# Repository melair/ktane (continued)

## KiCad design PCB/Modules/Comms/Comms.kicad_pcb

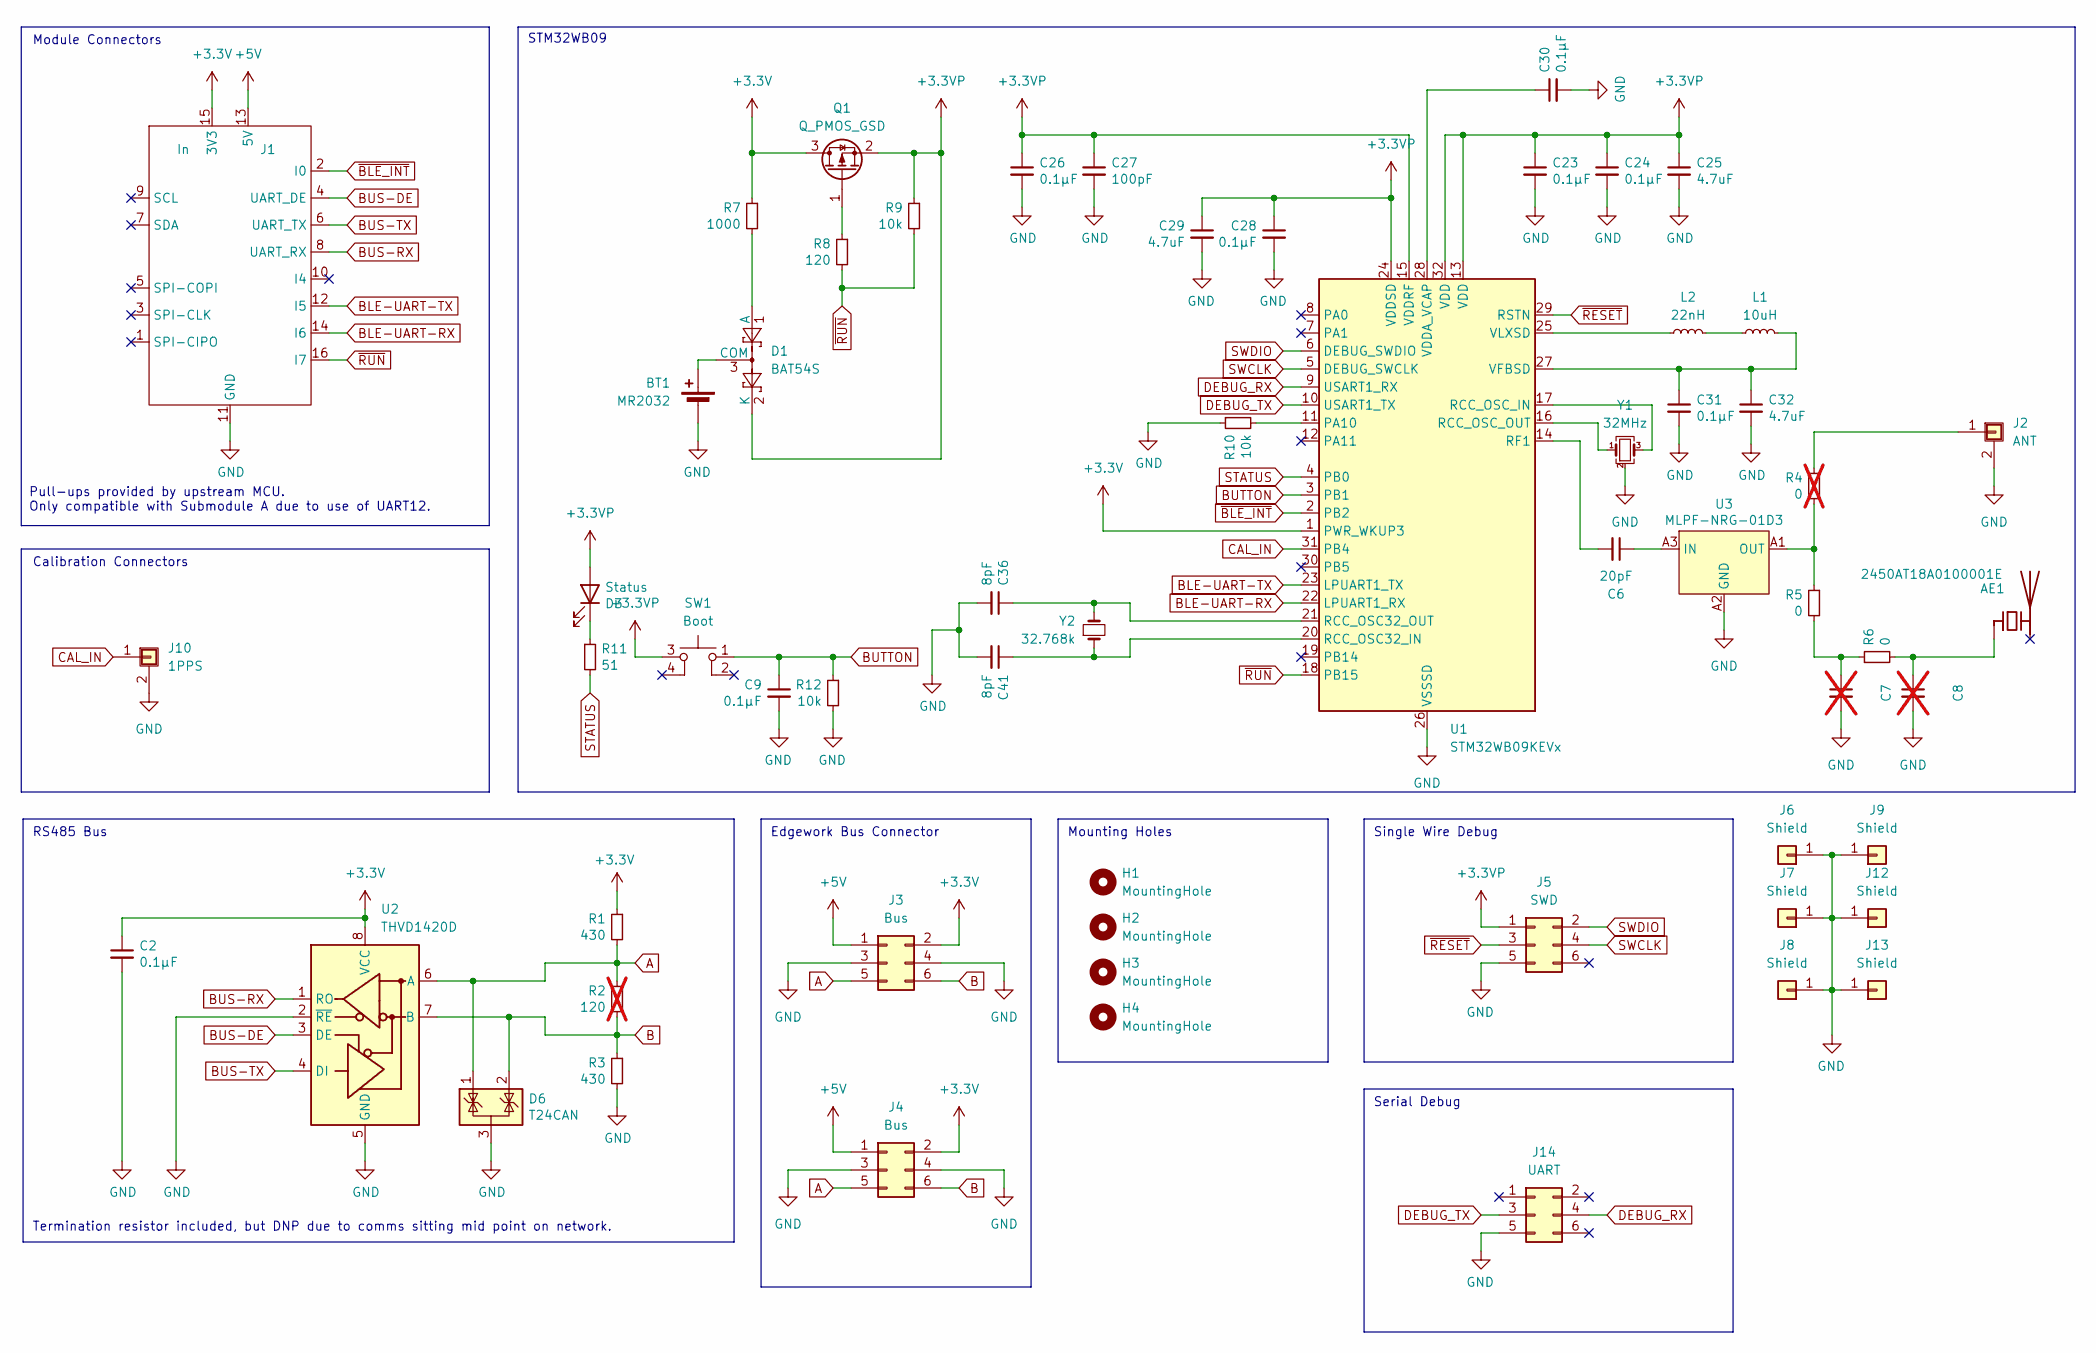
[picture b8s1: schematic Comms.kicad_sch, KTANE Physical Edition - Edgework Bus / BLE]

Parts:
AE1: 2450AT18A0100001E; Johanson_2450AT18x100_2400-2500Mhz; DIGIKEY 712-2450AT18A0100001ECT-ND
BT1: MR2032; CellHolder
C2, C9, C23, C24, C26, C28, C30, C31: 0.1μF; C_0603_1608Metric; DIGIKEY 1276-1005-1-ND
C6: 20pF; R_0402_1005Metric_Tweaked; DIGIKEY 1276-6601-1-ND
C7, C8: R_0402_1005Metric_Tweaked; DIGIKEY NONE; not fitted
C25, C29, C32: 4.7uF; C_0603_1608Metric; DIGIKEY 1276-2087-1-ND
C27: 100pF; C_0603_1608Metric; DIGIKEY 1276-1005-1-ND
C36, C41: 8pF; C_0603_1608Metric; DIGIKEY 490-GCM1885C2A8R0BA16JCT-ND
D1: BAT54S; SOT-23; DIGIKEY BAT54SLT1GOSCT-ND
D3: Status; LED_0603_1608Metric; DIGIKEY 160-1827-1-ND
D6: T24CAN; SOT-23; DIGIKEY STOCK
H1, H2, H3, H4: MountingHole; MountingHole_3.2mm_M3_NoCopper; DIGIKEY NONE
J1: In; PinHeader_2x08_P2.54mm_Vertical-Centered; DIGIKEY S9171-ND
J2: ANT; U.FL_Hirose_U.FL-R-SMT-1_Vertical; DIGIKEY 26-U.FL-R-SMT-1(32)CT-ND
J3, J4: Bus; PinHeader_2x03_P2.54mm_Vertical-Centered; DIGIKEY S9716-ND
J5: SWD; Tag-Connect_TC2030-IDC-NL_2x03_P1.27mm_Vertical; DIGIKEY NONE
J6, J7, J8, J9: Shield; EMI_Shield_Corner; DIGIKEY STOCK/AliExpress
J10: 1PPS; U.FL_Hirose_U.FL-R-SMT-1_Vertical; DIGIKEY 26-U.FL-R-SMT-1(32)CT-ND
J12, J13: Shield; EMI_Shield_Straight; DIGIKEY STOCK/AliExpress
J14: UART; Tag-Connect_TC2030-IDC-NL_2x03_P1.27mm_Vertical; DIGIKEY NONE
L1: 10uH; L_0805_2012Metric; DIGIKEY 490-LQM21DN100M70LCT-ND
L2: 22nH; L_0402_1005Metric; DIGIKEY 490-LQG15HN22NG02DCT-ND
Q1: Q_PMOS_GSD; SOT-23; DIGIKEY 4518-SI2307ACT-ND
R1, R3: 430; R_0603_1608Metric; DIGIKEY P430HCT-ND
R2: 120; R_0603_1608Metric; DIGIKEY P120HCT-ND; not fitted
R4: 0; R_0402_1005Metric_Tweaked; DIGIKEY 10-ERJ-H2G0R00XCT-ND; not fitted
R5, R6: 0; R_0402_1005Metric_Tweaked; DIGIKEY 10-ERJ-H2G0R00XCT-ND
R7: 1000; R_0603_1608Metric; DIGIKEY P1.00KHCT-ND
R8: 120; R_0603_1608Metric; DIGIKEY P120HCT-ND
R9, R10, R12: 10k; R_0603_1608Metric; DIGIKEY P10.0KHCT-ND
R11: 51; R_0603_1608Metric; DIGIKEY P51.0HCT-ND
SW1: Boot; PTS526Sx15SMTR2xLFS; DIGIKEY CKN12220-1-ND
U1: STM32WB09KEVx; QFN-32-1EP_5x5mm_P0.5mm_EP3.7x3.7mm; DIGIKEY 497-STM32WB09KEV6TRCT-ND
U2: THVD1420D; SOT-583-8; DIGIKEY 296-THVD1420DRLRCT-ND
U3: MLPF-NRG-01D3; DIGIKEY 497-MLPF-NRG-01D3CT-ND
Y1: 32MHz; Crystal_SMD_2016-4Pin_2.0x1.6mm; DIGIKEY 644-CS06654-32MCT-ND
Y2: 32.768k; Crystal_SMD_2012-2Pin_2.0x1.2mm; DIGIKEY XC3096CT-ND

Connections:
+3.3V: C2.1, J1.15 (3V3), J3.2, J4.2, Q1.3 (D), R1.1, R7.1, U1.1 (PWR_WKUP3), U2.8 (VCC)
+3.3VP: C23.1, C24.1, C25.1, C26.1, C27.1, C28.1, C29.1, D1.2 (K), D3.2 (A), J5.1, Q1.2 (S), R9.1, SW1.3, U1.13 (VDD), U1.15 (VDDRF), U1.24 (VDDSD), U1.32 (VDD)
+5V: J1.13 (5V), J3.1, J4.1
A: D6.1 (K), J3.5, J4.5, R1.2, R2.1, U2.6 (A)
B: D6.2 (K), J3.6, J4.6, R2.2, R3.1, U2.7 (B)
BLE-UART-RX: J1.14 (I6), U1.22 (LPUART1_RX)
BLE-UART-TX: J1.12 (I5), U1.23 (LPUART1_TX)
BUS-DE: J1.4 (UART_DE), U2.3 (DE)
BUS-RX: J1.8 (UART_RX), U2.1 (RO)
BUS-TX: J1.6 (UART_TX), U2.4 (DI)
BUTTON: C9.1, R12.1, SW1.1, U1.3 (PB1)
CAL_IN: J10.1, U1.31 (PB4)
DEBUG_RX: J14.4, U1.9 (USART1_RX)
DEBUG_TX: J14.3, U1.10 (USART1_TX)
GND: BT1.2 (-), C2.2, C7.2, C8.2, C9.2, C23.2, C24.2, C25.2, C26.2, C27.2, C28.2, C29.2, C30.2, C31.2, C32.2, C36.2, C41.2, D6.3 (A), J1.11 (GND), J2.2 (Shield), J3.3, J3.4, J4.3, J4.4, J5.5, J6.1 (Pin_1_1), J7.1 (Pin_1_1), J8.1 (Pin_1_1), J9.1 (Pin_1_1), J10.2 (Shield), J12.1 (Pin_1_1), J13.1 (Pin_1_1), J14.5, R3.2, R10.1, R12.2, U1.26 (VSSSD), U1.33 (VSSSD), U2.2 (~RE), U2.5 (GND), U3.A2 (GND), U3.B1 (GND), U3.B2 (GND), U3.B3 (GND), Y1.2 (G), Y1.4 (G)
unnamed: AE1.1 (FEED_1), C8.1, R6.2
unnamed: BT1.1 (+), D1.3 (COM)
unnamed: C7.1, R5.2, R6.1
unnamed: D1.1 (A), R7.2
unnamed: D3.1 (K), R11.1
unnamed: J2.1, R4.1
unnamed: L1.2, L2.1
unnamed: Q1.1 (G), R8.1
unnamed: U1.17 (RCC_OSC_IN), Y1.3
unnamed: U1.16 (RCC_OSC_OUT), Y1.1
unnamed: R10.2, U1.11 (PA10)
unnamed: C36.1, U1.21 (RCC_OSC32_OUT), Y2.2
unnamed: C41.1, U1.20 (RCC_OSC32_IN), Y2.1
unnamed: C6.2, U1.14 (RF1)
unnamed: C30.1, U1.28 (VDDA_VCAP)
unnamed: C31.1, C32.1, L1.1, U1.27 (VFBSD)
unnamed: L2.2, U1.25 (VLXSD)
unnamed: C6.1, U3.A3 (IN)
unnamed: R4.2, R5.1, U3.A1 (OUT)
STATUS: R11.2, U1.4 (PB0)
SWCLK: J5.4, U1.5 (DEBUG_SWCLK)
SWDIO: J5.2, U1.6 (DEBUG_SWDIO)
~BLE_INT: J1.2 (I0), U1.2 (PB2)
~RESET: J5.3, U1.29 (RSTN)
~RUN: J1.16 (I7), R8.2, R9.2, U1.18 (PB15)

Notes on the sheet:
Pull-ups provided by upstream MCU. Only compatible with Submodule A due to use of UART12.
Single Wire Debug
RS485 Bus
Module Connectors
Termination resistor included, but DNP due to comms sitting mid point on network.
Serial Debug
Mounting Holes
STM32WB09
Calibration Connectors
Edgework Bus Connector

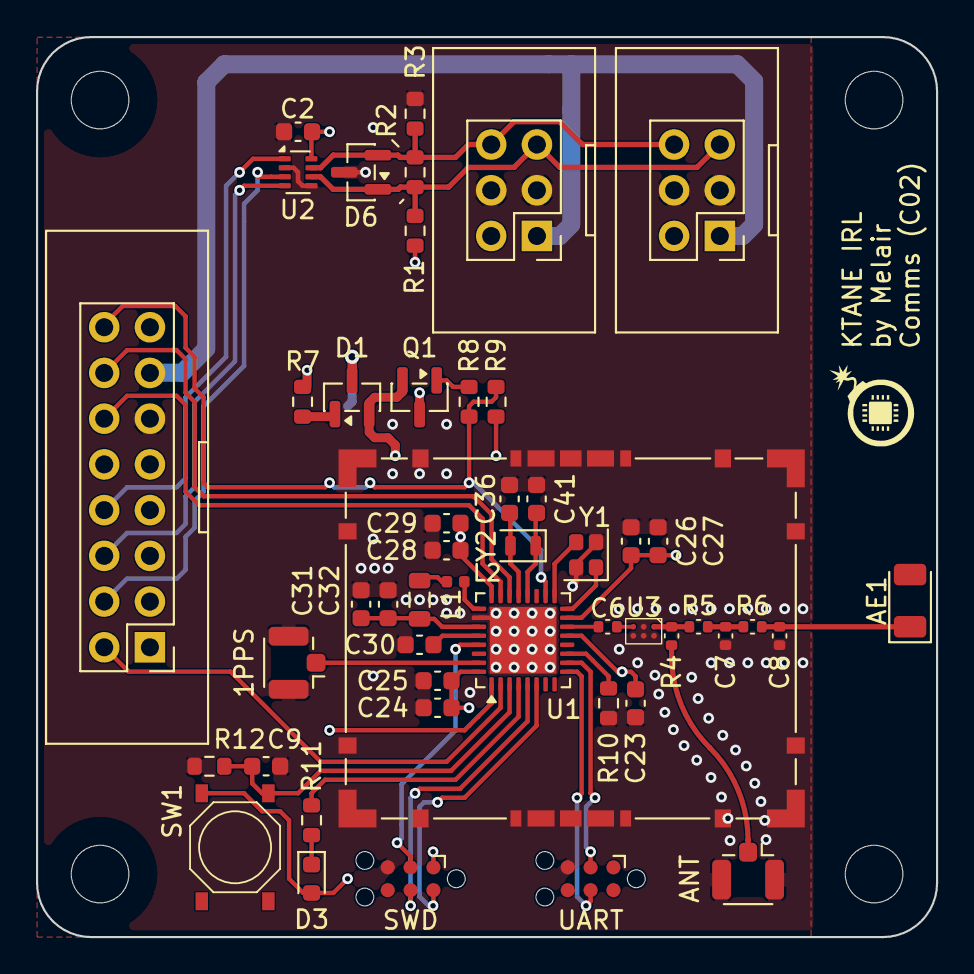
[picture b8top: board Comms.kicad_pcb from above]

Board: 4 copper layers, 50.0 x 50.0 mm, 60 parts (1 on the bottom side), 40 nets.

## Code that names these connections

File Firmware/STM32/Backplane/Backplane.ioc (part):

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Mcu.Name=STM32G070KBTx
Mcu.Package=LQFP32
Mcu.UserName=STM32G070KBTx
PA0.GPIOParameters=GPIO_Label
PA0.GPIO_Label=REAR_UART_TX
PA0.Mode=Asynchronous
PA0.Signal=USART4_TX
PA1.GPIOParameters=GPIO_Label
PA1.GPIO_Label=REAR_UART_RX
PA1.Mode=Asynchronous
PA1.Signal=USART4_RX
PA10.GPIOParameters=GPIO_Label
PA10.GPIO_Label=FRONT_UART_RX
PA10.Mode=Asynchronous
PA10.Signal=USART1_RX
PA11\ [PA9].GPIOParameters=GPIO_Label
PA11\ [PA9].GPIO_Label=FRONT_EFUSE_FLT
PA11\ [PA9].Signal=GPIO_Input
PA12\ [PA10].GPIOParameters=GPIO_Label
PA12\ [PA10].GPIO_Label=FRONT_EFUSE_EN
PA12\ [PA10].Signal=GPIO_Output
PA13.Mode=Serial_Wire
PA13.Signal=SYS_SWDIO
PA14-BOOT0.Mode=Serial_Wire
PA14-BOOT0.Signal=SYS_SWCLK
PA2.GPIOParameters=GPIO_Label
PA2.GPIO_Label=REAR_BOOT
PA2.Signal=GPIO_Output
PA3.GPIOParameters=GPIO_Label
PA3.GPIO_Label=REAR_ILM
PA3.Mode=IN3
PA3.Signal=ADC1_IN3
PA4.GPIOParameters=GPIO_Label
PA4.GPIO_Label=BOOT
PA4.Signal=GPIO_Input
PA5.GPIOParameters=GPIO_Label
PA5.GPIO_Label=BUS_TX
PA5.Mode=Asynchronous
PA5.Signal=USART3_TX
PA6.GPIOParameters=GPIO_Label
PA6.GPIO_Label=STATUS_LED
PA6.Signal=GPIO_Output
PA8.GPIOParameters=GPIO_Label
PA8.GPIO_Label=FRONT_MODULE_DETECT
PA8.Signal=GPIO_Input
PA9.GPIOParameters=GPIO_Label
PA9.GPIO_Label=FRONT_UART_TX
PA9.Mode=Asynchronous
PA9.Signal=USART1_TX
PB0.GPIOParameters=GPIO_Label
PB0.GPIO_Label=BUS_RX
PB0.Mode=Asynchronous
PB0.Signal=USART3_RX
PB1.GPIOParameters=GPIO_Label
PB1.GPIO_Label=BUS_DE
PB1.Mode=Hardware Flow Control (RS485)
PB1.Signal=USART3_DE
PB2.GPIOParameters=GPIO_Label
PB2.GPIO_Label=FRONT_ILM
PB2.Mode=IN10
PB2.Signal=ADC1_IN10
PB6.Mode=I2C
PB6.Signal=I2C1_SCL
PB7.Mode=I2C
PB7.Signal=I2C1_SDA
PB9.GPIOParameters=GPIO_Label
PB9.GPIO_Label=REAR_EFUSE_FLT
PB9.Signal=GPIO_Input
PC14-OSC32_IN\ (PC14).GPIOParameters=GPIO_Label
PC14-OSC32_IN\ (PC14).GPIO_Label=REAR_EFUSE_EN
PC14-OSC32_IN\ (PC14).Signal=GPIO_Output
PC15-OSC32_OUT\ (PC15).GPIOParameters=GPIO_Label
PC15-OSC32_OUT\ (PC15).GPIO_Label=REAR_MODULE_DETECT
PC15-OSC32_OUT\ (PC15).Signal=GPIO_Input
PC6.GPIOParameters=GPIO_Label
PC6.GPIO_Label=FRONT_BOOT
PC6.Signal=GPIO_Output
RCC.HSE_VALUE=8000000
RCC.SYSCLKFreq_VALUE=64000000
RCC.SYSCLKSource=RCC_SYSCLKSOURCE_PLLCLK
board=custom

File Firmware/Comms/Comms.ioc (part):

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Mcu.Name=STM32WB09KEVx
Mcu.Package=VFQFPN32
Mcu.UserName=STM32WB09KEVx
PA0.Mode=I2C
PA0.Signal=I2C1_SCL
PA1.Mode=I2C
PA1.Signal=I2C1_SDA
PA11.Mode=Full_Duplex_Slave
PA11.Signal=SPI3_MOSI
PA2.Mode=Serial_Wire
PA2.Signal=DEBUG_SWDIO
PA3.Mode=Serial_Wire
PA3.Signal=DEBUG_SWCLK
PA8.Mode=Full_Duplex_Slave
PA8.Signal=SPI3_MISO
PA9.Mode=NSS_Signal_Hard_Input
PA9.Signal=SPI3_NSS
PB0.Mode=WakeUp0
PB0.Signal=PWR_WKUP0
PB12.Mode=LSE-External-Oscillator
PB12.Signal=RCC_OSC32_OUT
PB13.Mode=LSE-External-Oscillator
PB13.Signal=RCC_OSC32_IN
PB14.Mode=Clock-out
PB14.Signal=RCC_MCO
PB2.GPIOParameters=GPIO_Label
PB2.GPIO_Label=BLE_INT
PB2.Signal=GPIO_Input
PB3.Mode=Full_Duplex_Slave
PB3.Signal=SPI3_SCK
PB4.GPIOParameters=GPIO_Label
PB4.GPIO_Label=CAL_IN
PB4.Signal=S_TIM2_CH1
PB5.GPIOParameters=GPIO_Label
PB5.GPIO_Label=RUN
PB5.Signal=GPIO_Output
PB6.Mode=Asynchronous
PB6.Signal=LPUART1_TX
PB7.Mode=Asynchronous
PB7.Signal=LPUART1_RX
RCC.HSE_VALUE=32000000
RCC.SYSCLKSource=RCC_SYSCLKSOURCE_DIRECT_HSE
board=custom

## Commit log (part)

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2021-08-25 Fix bug with game seed being reset every time a status message was received.
2021-08-25 Rework wires to use standard colours, and functions to calculate the solution. Unimplemented.
2021-08-25 Add implementation for simple wires, logic for which wire to cut.
2021-08-25 Minor whitespace formatting.
2021-08-27 Have password and who's on first modules clear screen on completion.
2021-08-27 Change Simon Says to be full brightness but turn off light on beep.
2021-08-27 At 3 second startup delay when all is ready, play time to 5 minutes, strikes to 3.
2021-08-27 Misc changes and firmware version bump.
2021-08-27 Fix bug in display with words with spaces in who's on first.
2021-09-01 Add needy flag and common function for detecting if all enabled modules that aren't needy are done.
2021-09-01 Fix compilation errors with end game and needy function header.
2022-08-26 Rework wire detection to only care about disconnections, not colour changes during play.
2022-08-30 Add fixes, add rotary encoder, combination lock add edgework browser.
2022-09-04 Tweak maximum number of modules online, fix mode count.
2022-09-16 Migrate combination local variables to mode union.
2022-09-16 Add NVM functionality to read/write to the program space.
2022-09-16 Add support for CAN auto addressing.
    This also adds an INIT state which modules sit in pre CAN address assignment.
2022-09-16 Add KiCad 6 project files.
2022-09-16 Add new Power Management PCB.
2022-09-16 Add missed OPCODE refactor.
2022-12-18 Add concept of domain for CAN bus, to be used with 2.4GHz chassis link.
2022-12-18 New module with RTC, uSD card and nf24 radio, all using SPI.
2022-12-18 Update PullUpDown module with updated KiCad files (recovery/upgrade).
2023-02-05 Allow users of keymatrix to specify debounce samples.
2023-02-05 Redisable IOC.
2023-02-05 Add operator acrylic.
2023-02-05 Seperate controller main functionality and LCD UI.
2023-02-05 Add missing ui files.
2023-02-05 Remove mode override.
2023-02-12 Add UI for controller for debug, fix up bugin error handling, lint whitespace.
2023-02-12 Add ability to change the mode of a module via configuration menu.
2023-02-12 Only initialise LCD display if module uses it.
2023-02-15 Initial pass at audio peripheral.
2023-02-15 Move LCD into peripherals.
2023-02-20 Migrate segment peripheral to generic peripherals directory.
2023-02-20 First untested pass at SPI controller.
2023-02-21 Add kpin functions for PPS.
2023-02-21 Migrate SPI to use new KPORT.
2023-02-27 Add manual pages for keys, operator and combination.
2023-02-27 Add images for CardScan cards.
2023-02-27 Add card scan image readme.
2023-03-03 Split apart cardscan into logical pieces.
2023-03-04 Add cooldown for card reads based on UID at 2.5s, new cards can be read instantly due to new UID.
2023-03-04 Fix LCD number display, refactor module data into mode_data.
2023-03-04 Add ability to invoke special functions from controller to module, migrate cardscan.
2023-03-06 First pass at card scan module complete, readd ability to start game via UI, expose defining new characters for LCD.
2023-03-06 Add missed memory updates for Card Scan.
2023-03-07 Remove debug module.
2023-03-07 Add game completion logic handling for enabled modules.
2023-03-08 Add handling for enable/disable, shift cardscan programming to IDLE only phase.
2023-03-09 Fix up handling of state changes.
2023-03-09 Add support for disabling modules.
2023-03-10 Migrate ARGB to SPI abstraction, add delayed CS, initial opts work.
2023-03-11 Bump firmware version.
2023-03-13 Fix up SPI HAL to be more scalable, move pins into HAL. Implement RTC clock reading on optional module.
2023-03-26 Rework audio mixing to rely on service loop, optomise sample mixing, ensure audio fill request timer fires interrupt to wake from sleep.
2023-03-27 Add better tooling for sd card, add sdcard resources, updates FAT docs, add port usage tracking.
2023-03-27 Fix tab in bootloader.c
2023-03-27 Add framework for flasher firmware, offset at 0x01F000, for #13.
2023-03-27 Allow PPS to be changed multiple times.
2023-03-27 Migrate existing firmware to new location and rename.
2023-03-27 Begin to form unified application, fix known issues with function pointers, fix sd card init bug.
2023-03-27 Remove mux play command, used for testing, accidentally committed.
2023-03-29 Migrate EEPROM addresses to shared, segment offset/sizes, tweak buzzer debug disable.
2023-03-31 Extract NVM routines out to common directory, fix bug with eeprom.
    Previous initialisation of the EEPROM could result in a power off after the version
    is written but before the migration, resulting it 0xff data being returned rather
    than the migrated data.
    Move version set to after migrations.
2023-03-31 Remove existing firmware_get_version and const, update nvm for CCI.
2023-04-01 Flesh out new firmware functions.
2023-04-02 Adjust firmware protocol to handle segments, broadcast versions of all segments, store in module data, remove old flashing routines.
2023-04-02 Remove restriction of controllers being only source of firmware, use nvm_*() functions in fw.c.
2023-04-04 Begin migration of CAN into common.
2023-04-05 Complete structure definitions of packets.
2023-04-07 Untested WIP, migrate packet handling to new dynamic system, move logic around where appropriate to subsystems that interact with packets.
2023-04-09 Fix bug with firmware updating, where it would ALWAYS firmware.
2023-04-10 Fix version endian (again), bootloader size, migrate to global incomming packet_t*
    Because the packet handlers for modules are called by a function pointer, it appears
    that XC8 does not correctly locate the parameters passed in, as such they are
    corrupted as soon as the function starts.
    This does argue against this approach and perhaps it should be migrated back to
    a statically linked set of functions. Using #define to include the routers for
    prefixes.
2023-04-12 Fix forced strike bug, adjust simon timings to be closer to game.
2023-04-14 Fix combination bug, add config for ARGB brightness and buzzer vol, add custom game type menus.
2023-04-16 Add additional direction arrows to manual.
2023-04-16 Fix bug with edgework vowel detection on successive games.
    Once the module had played a round with a serial number that has a vowel, it would
    incorrectly assume that every future round had a vowel. As the init value was
    only being reset to false at boot, it's now done each time the edgework is
    calculated.
2023-04-16 Create generic functions for determining number of solved/enabled modules/puzzles.
2023-04-16 Improve documentation clarity, credit Starlett/@insiderphd.
2023-04-16 Migrate more module counting to use module_ functions.
2023-04-18 Add initial support for I2C abstraction, power management board via I2C.
2023-04-21 Add config UI for opts.
2023-04-23 Second round of compiler fixes.
2023-04-25 Replace buzzer calls with start of sound system.
2023-05-07 Fleshout sound support, add FAT, remote play, dynamic memory/malloc.
2023-08-03 Migrate audio output to H-bridge over DAC.
2023-08-20 Add audio for operator rework.
2023-08-24 Fix up sounds, add DAC volume, fix power mgmt and display.
2023-08-29 Add doc page for Card Scan.
2023-08-29 Rework of operator module, untested.
2023-08-29 Add prototype for LCD module.
2023-08-29 Add .gitignore for PCB file types.
2023-09-01 Beginning rework of Control Board for respin.
2023-09-03 Fix combined image configuration after migration to 2.41.
2023-09-03 Remove redundant struct.
2023-09-03 Add debug handling to packet handler.
2024-08-26 Initial work on debug packets.
2024-08-26 Fix up support for debug packets.
2024-08-26 Fix extremely broken power status display logic.
2026-03-13 Remove legacy PCBs from V1.
2026-03-13 Update libraries to new V2 layouts.
2026-03-13 ControlBoard B02, with buck regulator fix.
2026-03-13 First pass of PCB rework.
2026-03-13 Add audio module.
2026-03-13 Add manual page for Ending the World.
2026-03-13 Add timer display and strike display.
2026-03-13 WIP: LCD Driver for Maze.
2026-03-13 WIP: Power management.
2026-03-13 Update gitignore for macos.
2026-03-14 Add initial VS Code MPLAB projects for Bootloader and ControlBoard.
2026-03-16 Add common library, fleshout basic bootloader.
2026-03-16 Define application locations via defines, add readme's with more info.
2026-03-18 Add basic MCU init, interrupt init, and pin HAL.
2026-03-20 First pass of FSM.
2026-03-21 First pass at SPI hal, however is huge once compiled.
2026-03-21 Rework SPI to only allow single instantiation, but take SPI port from compiler micro. 65% smaller build.
2026-03-22 Fix up SPI HAL, read and write appear to work.
2026-03-22 Add time system based in 0.5ms intervals.
2026-03-24 First pass at initialising ePaper screen.
2026-03-24 Initial work on draw operations.
2026-03-24 Generify stacking commands and data to the epaper screen.
2026-03-25 WIP: Identifying how to address epaper.
2026-03-25 Fix up comments.
2026-03-25 Fix up comments (again).
2026-03-25 Correct rotation 180.
2026-03-26 Add ESD protection to the RS485 networks.
2026-03-27 Fix up power LEDs on regulators.
2026-03-27 Import SERIAL# begin rotation diagnostics.
2026-03-28 WIP: Rework x2/y2 into width/height.
2026-03-28 Import bolder font for serial number, add support for b/w only panels.
2026-03-31 Include all corrections, mint new gerbers. Update some to KiCad 10.
2026-04-08 Correct Digikey part numbers.
2026-04-09 Basic power handling with eFuse.
2026-04-09 Push DMA selection for SPI to compile flags.
2026-04-11 Update SPI state names to remove clashes, ensure pins are only configured if present.
2026-04-11 Increase chase to 16 bits.
2026-04-11 Test I2C in edgework.
2026-04-11 Update some files to KiCad 10.
2026-04-11 Tidy up Edgework, add serial label and font to Common.
2026-04-11 Harden up FSM implementation.
2026-04-11 Make spi_transaction_t not mutated, add guards.
2026-04-11 Remove modulo from time tracking, computationally expensive.
2026-04-11 Make access to internal_tick in timer atomic.
2026-04-11 Start of ARGB code.
2026-04-11 WIP: ARGB implementation.
2026-04-12 Tidy up ARGB, debug issues with FSM and XC8 compilation.
2026-04-12 Remove fs_t name, fix corruption bug in argb_set.
2026-04-13 Remove temporary set up for ARGB from edgework.
2026-04-14 Add support for setting current via I2C.
2026-04-15 Begin CSP implementation, add DMA/PPS/CLC tables to polyfill.
2026-04-17 More CSP work, add testing for strikes.
2026-04-18 Working example of driving strikes and timer.
2026-04-18 Remove strike testing.
2026-04-18 Fix holes in CSP implementation.
2026-04-18 Add more metrics, catch deadlock and runts.
2026-04-21 Initial implementation of base CAN interface.
2026-04-23 Fix deadlock after single CAN node running. Other safety tweaks.
2026-04-23 Add RNG and unique ID code.
2026-04-27 Add implementation for status/button control, plus keymatrix.
2026-04-27 Fix up minor bugs and typos.
2026-04-28 Clean up object init, add COBS implementation (untested) to CSP.
2026-04-29 Update to KiCad 10.
2026-05-01 Add template modes for other modes.
2026-05-23 End of PIC18 development for firmware, migration to STM32 hardware will occur.
2026-06-24 feat: Rework ControlBoard to use an STM32H562VGT6.
2026-06-25 feat: Upgrade backplane to a STM32G070KB.
2026-06-25 feat: Migrate edgework to a STM32G070KBT6.
2026-06-25 feat: Update audio board to consume I2S from STM32 parent board, removing ESP32.
2026-06-26 feat: Add support for battery for RTC on comms board.
2026-06-26 feat: Remove backup battery for RTC, and crystal. 1PPS can be derived from HSE.
2026-06-27 fix: Correct stitching for 3.3V and GND layers.
2026-06-27 chore: Add updated project.
2026-06-27 feat: Initial start of STM32 projects for firmware.
2026-06-27 feat: Configure initial peripherals on STM32H5.
2026-06-27 feat: Configure RTC clock from HSE.
2026-06-27 feat: Clock bus UART off of 32MHz HSI.
2026-06-27 feat: Import legacy BOMs for old boards.
2026-06-27 feat: Replace bare pads for battery with a cell, incase we want to use a cell holder.
2026-06-27 fix: VDD pour broken by LED, move, resolve minor stitching errors.
2026-06-28 feat: Add peripheral config to other three MCUs.
2026-06-28 fix: Minor IOC tweaks.
